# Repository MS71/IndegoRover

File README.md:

# IndegoRover
new MainBoard for Indego Lawn Mower

Prototype:

Schematic:
https://github.com/MS71/IndegoRover/blob/main/kicad/IndegoMower/pdf/IndegoMower.pdf

PCB:

Parts:
* ESP32 (S2/S3) Module (https://github.com/MS71/ROS2Mower/blob/master/hw/esp32_module.pdf)
* ARV Mega 128 for low level IO, security and motor driver
* origonal Indego connectors (26SHC-B-1A => mouser)
* DC motor driver: 3 * VNH2SP30 module (41V, 30A H Bridge)
* GPS receiver (ZED-F9P) (https://www.ardusimple.com/product/simplertk2blite/)
* 5 pin header for low cost, non RTK GPS receiver
* 10 Pin RPI Connector (5V, 3.3V, GND, I2C, UART)
* 10 Pin I2C Bus Connector
* 6 Pin I2C Bus Connector
* 5V Step Down Converter
* Bat Charger Circuit (Compatible with Indego Charge Station, difficult)
* Bat Charger Circuit (Compatible with std. 36V solar panel)
* Coil Sensor Amp
* low power + standby
* support for all available sensors
* BNO055 IMU module headers
* support for all sensors (bumper, coil fensem ...)
* power supply for onboard computer
* beeper
* support for LCD and keyboard (difficult)
* some breadboard area for custom extensions
* ...

onboard ROS2 computer: (optional)
* RPI4 or RPI Zero 2W headers 
* Orange Pi Zero 2 headers (http://www.orangepi.org/Orange%20Pi%20Zero2/)
* ...

Other:
* made with free Eagle  (max. 80 qcm) or kicad6

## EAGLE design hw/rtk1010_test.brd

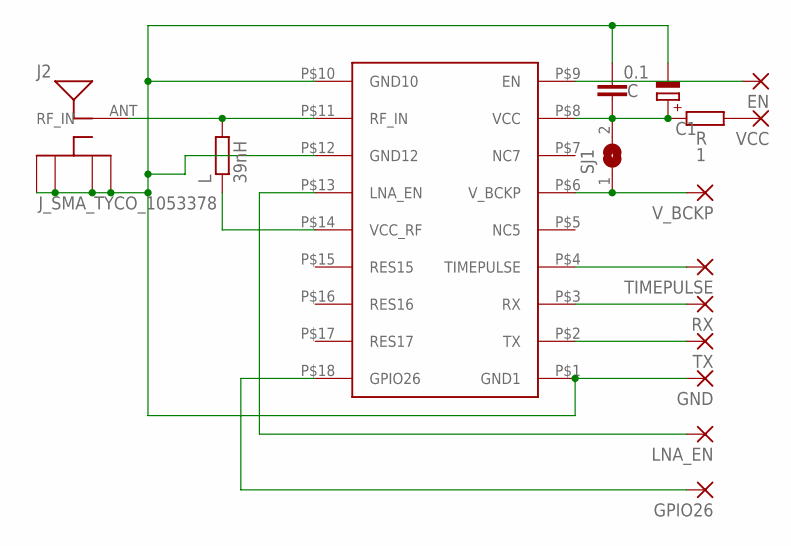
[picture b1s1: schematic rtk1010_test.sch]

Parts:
C: 0.1; C0805
C1: CPOL-EUSMCB; SMC_B
EN: 2,15/1,0
GND: 2,15/1,0
GPIO26: 2,15/1,0
J2: J_SMA_TYCO_1053378; 1053378-1
L: 39nH; R0805
LNA_EN: 2,15/1,0
R: 1; R0805
RX: 2,15/1,0
SJ1: SJW
TIMEPULSE: 2,15/1,0
TX: 2,15/1,0
U$1: RTK-1010
VCC: 2,15/1,0
V_BCKP: 2,15/1,0

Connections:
EN: EN.1, U$1.P$9 (EN)
GND: C.2, C1.-, GND.1, J2.GND_1 (RFGND_1), J2.GND_2 (RFGND_2), J2.GND_3 (RFGND_3), J2.GND_4 (RFGND_4), U$1.P$1 (GND1), U$1.P$10 (GND10), U$1.P$12 (GND12)
GPIO26: GPIO26.1, U$1.P$18 (GPIO26)
LNA_EN: LNA_EN.1, U$1.P$13 (LNA_EN)
unnamed: L.1, U$1.P$14 (VCC_RF)
unnamed: R.2, VCC.1
RF_IN: J2.ANT (RF_IN), L.2, U$1.P$11 (RF_IN)
RX: RX.1, U$1.P$3 (RX)
TIMEPULSE: TIMEPULSE.1, U$1.P$4 (TIMEPULSE)
TX: TX.1, U$1.P$2 (TX)
VCC: C.1, C1.+, R.1, SJ1.2, U$1.P$8 (VCC)
V_BKUP: SJ1.1, U$1.P$6 (V_BCKP), V_BCKP.1

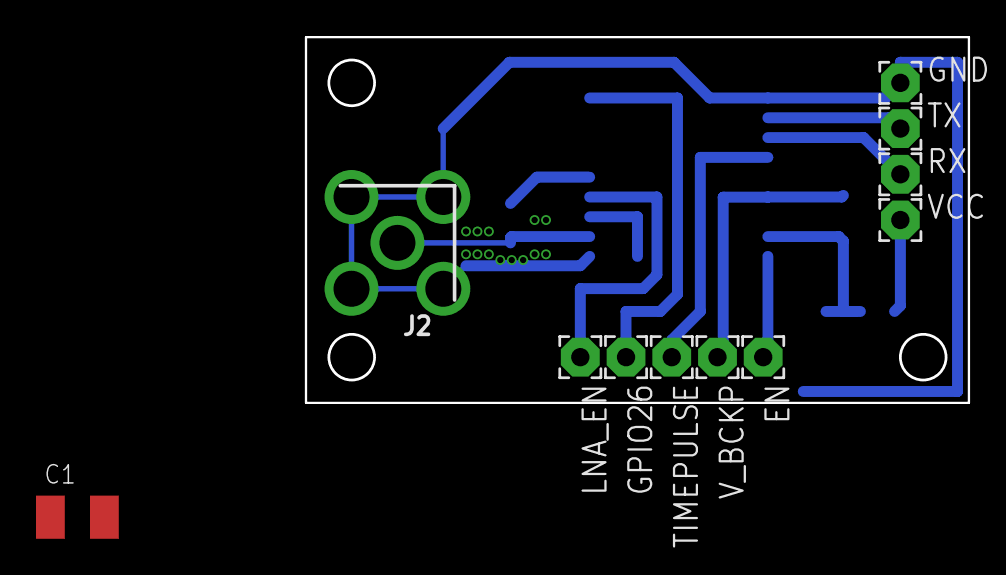
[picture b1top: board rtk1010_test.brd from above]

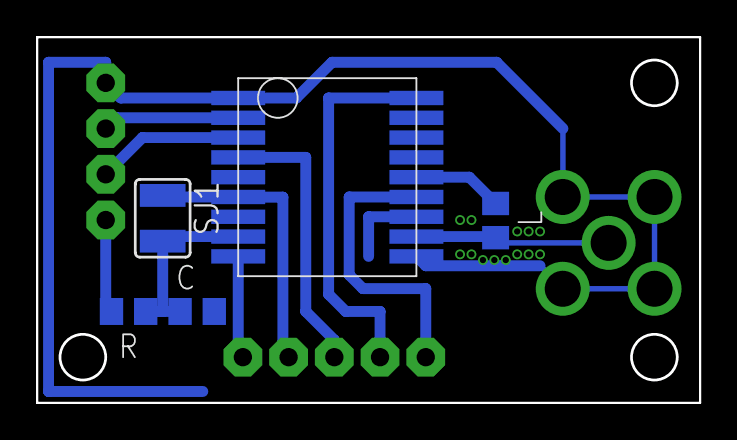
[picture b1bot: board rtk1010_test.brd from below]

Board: 2 copper layers, 36.8 x 20.3 mm, 16 parts (5 on the bottom side), 12 nets.

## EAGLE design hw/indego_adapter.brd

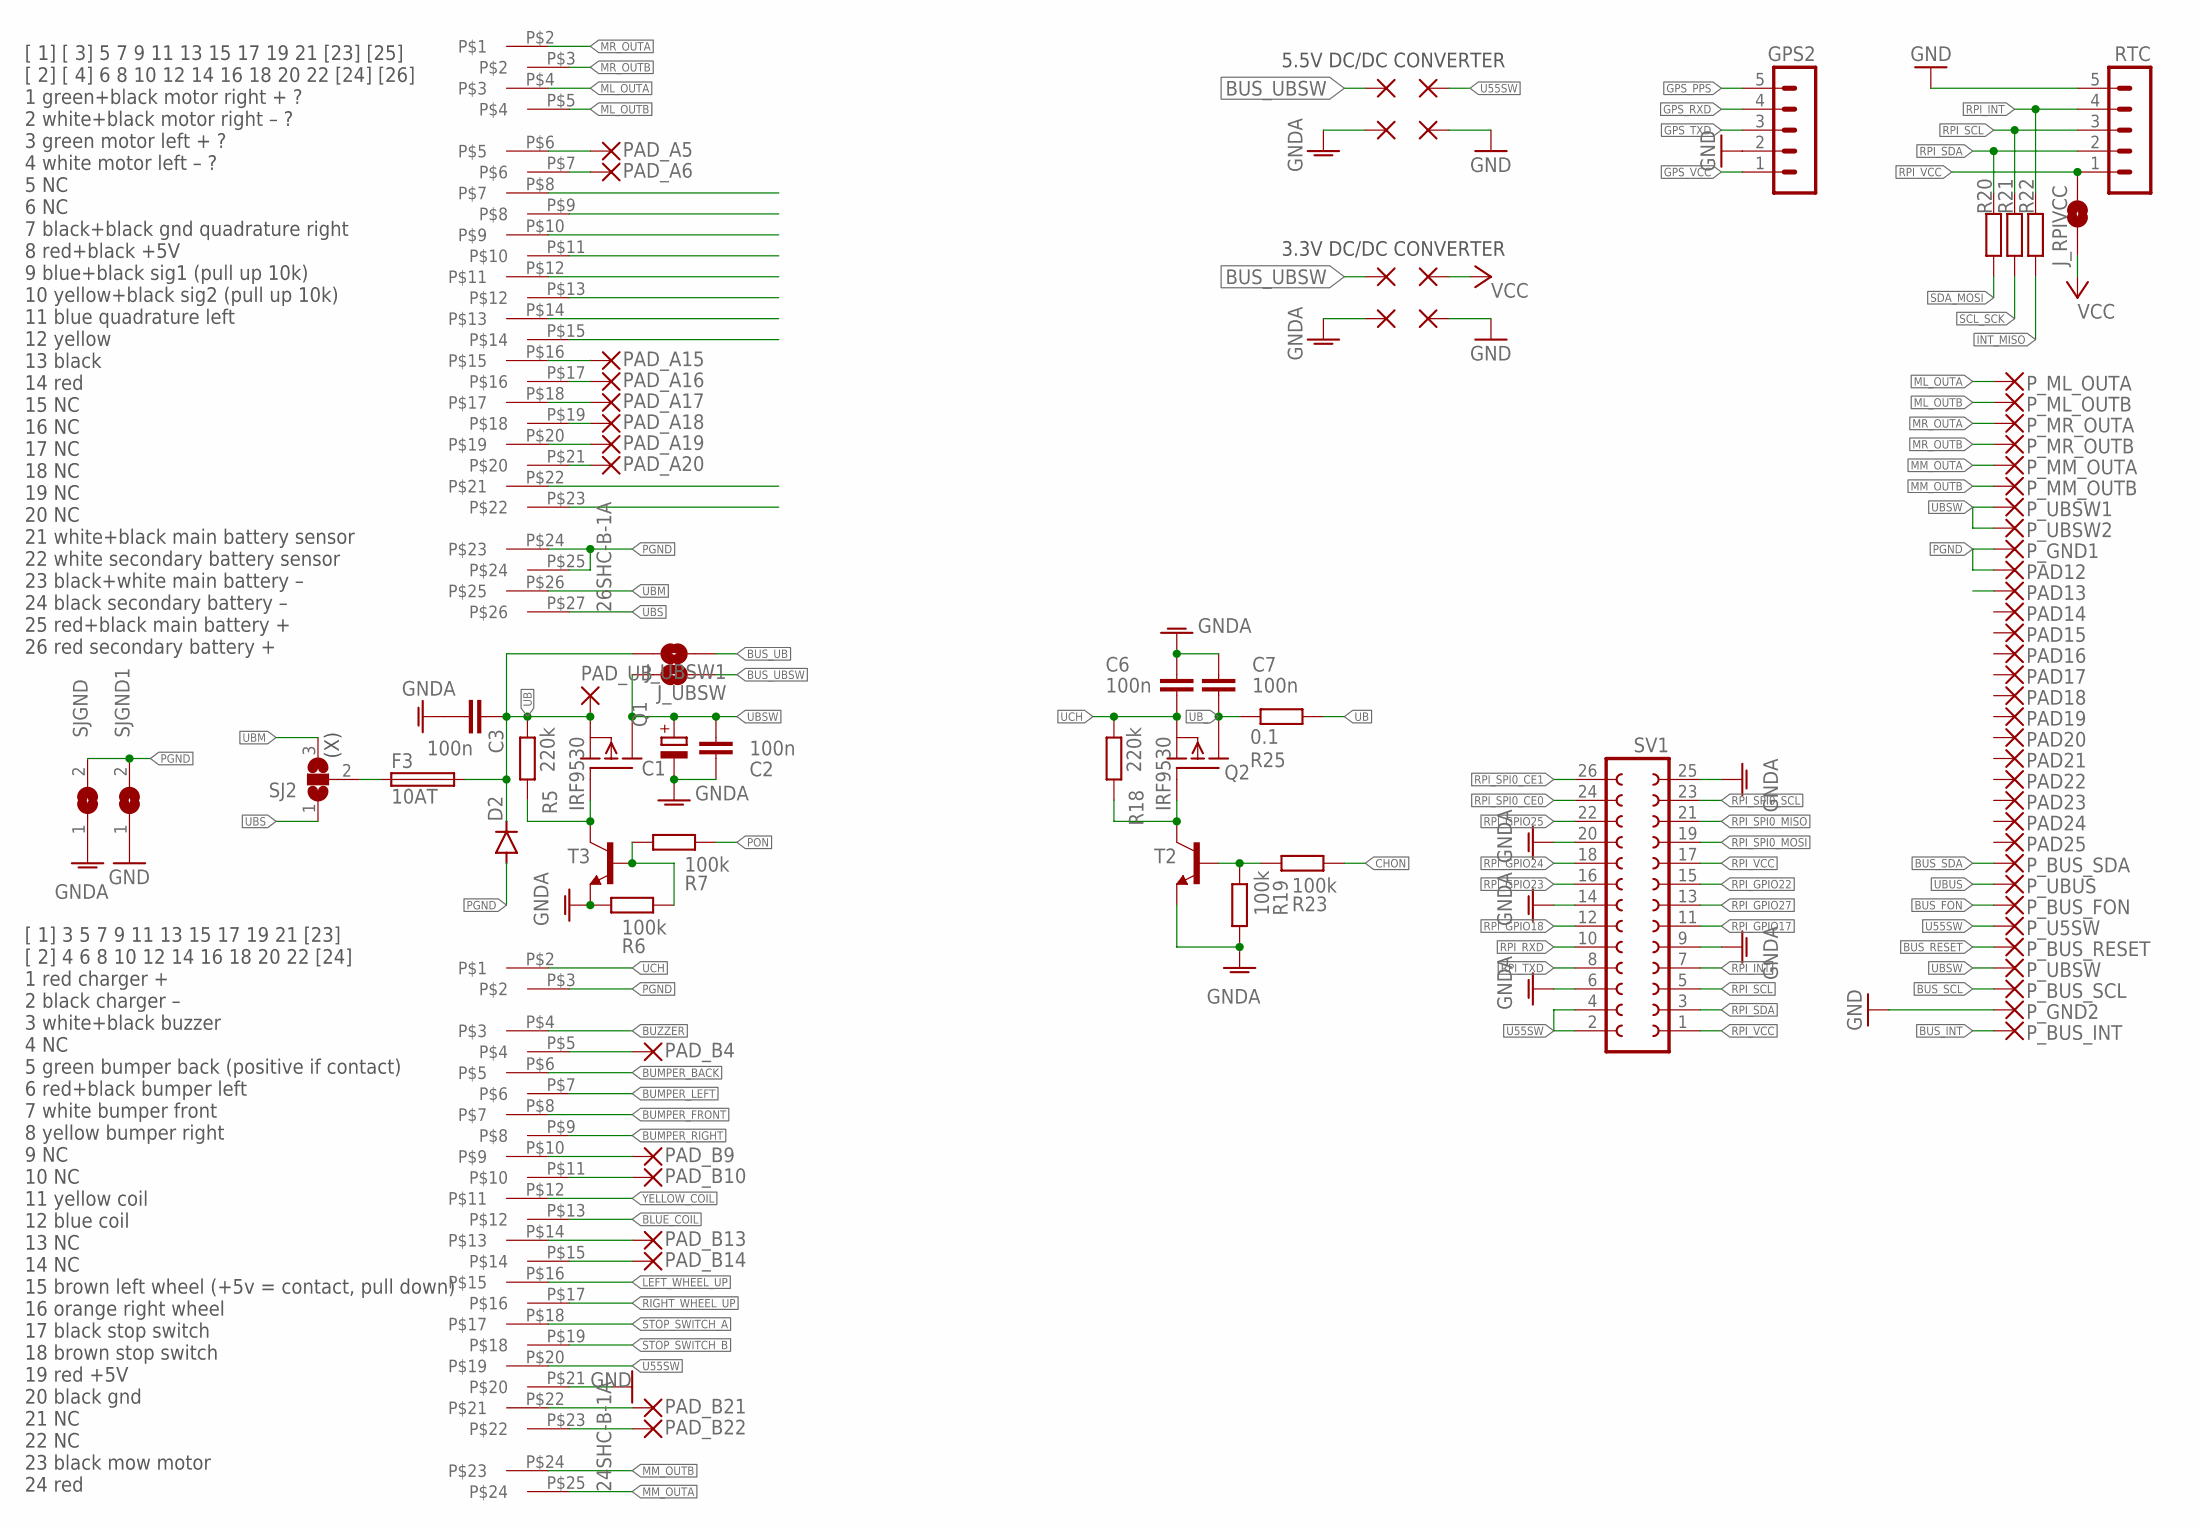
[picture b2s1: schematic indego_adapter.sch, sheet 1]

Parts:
C1: CPOL-EUE7.5-16; E7,5-16
C2, C3, C6, C7: 100n; C0805
D2: DIODE-MELF-MLL41; MELF-MLL41
DC_GND1, DC_GND2, DC_GND3, DC_GND4: 2,54/1,0
DC_VIN1, DC_VIN2: 2,54/1,0
F3: 10AT; SH22,5A
GPS2: MA05-1
J_RPIVCC: JUMPER-SMT_2_NO_NO-SILK; SMT-JUMPER_2_NO_NO-SILK
J_UBSW, J_UBSW1: JUMPER-SMT_2_NO_NO-SILK; SMT-JUMPER_2_NO_NO-SILK
PAD12, PAD13, PAD14, PAD15, PAD16, PAD17, PAD18, PAD19, PAD20, PAD21, PAD22, PAD23, PAD24, PAD25: 2,15/1,0
PAD_A5, PAD_A6, PAD_A15, PAD_A16, PAD_A17, PAD_A18, PAD_A19, PAD_A20: 1,6/0,9
PAD_B4, PAD_B9, PAD_B10, PAD_B13, PAD_B14, PAD_B21, PAD_B22: 1,6/0,9
PAD_UB: 3,17/1,3
P_BUS_FON: 2,15/1,0
P_BUS_INT: 2,15/1,0
P_BUS_RESET: 2,15/1,0
P_BUS_SCL: 2,15/1,0
P_BUS_SDA: 2,15/1,0
P_GND1, P_GND2: 2,15/1,0
P_ML_OUTA: 2,15/1,0
P_ML_OUTB: 2,15/1,0
P_MM_OUTA: 2,15/1,0
P_MM_OUTB: 2,15/1,0
P_MR_OUTA: 2,15/1,0
P_MR_OUTB: 2,15/1,0
P_U5SW: 2,15/1,0
P_UBSW, P_UBSW1, P_UBSW2: 2,15/1,0
P_UBUS: 2,15/1,0
Q1, Q2: IRF9530; TO220
R5, R18: 220k; R0805
R6, R7, R19, R23: 100k; R0805
R20, R21, R22: R-EU_M0805; M0805
R25: 0.1; R2512
RTC: MA05-1
SJ2: SJ2W; SJ_2
SJGND, SJGND1: SJ
SV1: FE13-2
T2, T3: BC817-16-NPN-SOT23-BEC; SOT23-BEC
U55SW: 2,54/1,0
U$1: 26SHC-B-1A
U$3: 24SHC-B-1A
VCC: 2,54/1,0

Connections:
BLUE_COIL: U$3.P$13
BUMPER_BACK: U$3.P$6
BUMPER_FRONT: U$3.P$8
BUMPER_LEFT: U$3.P$7
BUMPER_RIGHT: U$3.P$9
BUS_FON: P_BUS_FON.1; also elsewhere on the board
BUS_INT: P_BUS_INT.1; also elsewhere on the board
BUS_RESET: P_BUS_RESET.1; also elsewhere on the board
BUS_SCL: P_BUS_SCL.1; also elsewhere on the board
BUS_SDA: P_BUS_SDA.1; also elsewhere on the board
BUS_UB: J_UBSW1.2; also elsewhere on the board
BUS_UBSW: DC_VIN1.1, DC_VIN2.1, J_UBSW.2; also elsewhere on the board
BUZZER: U$3.P$4
CHON: R23.2
GND: DC_GND2.1, DC_GND4.1, GPS2.2, P_GND2.1, RTC.5, SJGND1.1, U$3.P$21; also elsewhere on the board
GNDA: C1.-, C2.2, C3.2, C6.1, C7.1, DC_GND1.1, DC_GND3.1, R6.1, R19.1, SJGND.1, SV1.6, SV1.9, SV1.14, SV1.20, SV1.25, T2.E, T3.E
GPS_PPS: GPS2.5
GPS_RXD: GPS2.4; also elsewhere on the board
GPS_TXD: GPS2.3; also elsewhere on the board
GPS_VCC: GPS2.1; also elsewhere on the board
INT_MISO: R22.1
LEFT_WHEEL_UP: U$3.P$16
ML_OUTA: P_ML_OUTA.1, U$1.P$4; also elsewhere on the board
ML_OUTB: P_ML_OUTB.1, U$1.P$5; also elsewhere on the board
MM_OUTA: P_MM_OUTA.1, U$3.P$25; also elsewhere on the board
MM_OUTB: P_MM_OUTB.1, U$3.P$24; also elsewhere on the board
MR_OUTA: P_MR_OUTA.1, U$1.P$2; also elsewhere on the board
MR_OUTB: P_MR_OUTB.1, U$1.P$3; also elsewhere on the board
unnamed: Q2.1 (G), R18.2, T2.C
unnamed: PAD_B4.1, U$3.P$5
unnamed: PAD_A5.1, U$1.P$6
unnamed: PAD_A6.1, U$1.P$7
unnamed: PAD_A15.1, U$1.P$16
unnamed: PAD_A16.1, U$1.P$17
unnamed: PAD_A17.1, U$1.P$18
unnamed: PAD_A18.1, U$1.P$19
unnamed: PAD_A19.1, U$1.P$20
unnamed: PAD_A20.1, U$1.P$21
unnamed: PAD_B9.1, U$3.P$10
unnamed: PAD_B10.1, U$3.P$11
unnamed: R6.2, R7.1, T3.B
unnamed: Q1.1 (G), R5.2, T3.C
unnamed: PAD_B13.1, U$3.P$14
unnamed: PAD_B14.1, U$3.P$15
unnamed: PAD_B21.1, U$3.P$22
unnamed: PAD_B22.1, U$3.P$23
unnamed: R19.2, R23.1, T2.B
PGND: D2.A, PAD12.1, P_GND1.1, SJGND.2, SJGND1.2, U$1.P$24, U$1.P$25, U$3.P$3; also elsewhere on the board
PON: R7.2
RIGHT_WHEEL_UP: U$3.P$17
RPI_GPIO17: SV1.11
RPI_GPIO18: SV1.12
RPI_GPIO22: SV1.15
RPI_GPIO23: SV1.16
RPI_GPIO24: SV1.18
RPI_GPIO25: SV1.22
RPI_GPIO27: SV1.13
RPI_INT: R22.2, RTC.4, SV1.7
RPI_RXD: SV1.10
RPI_SCL: R21.2, RTC.3, SV1.5
RPI_SDA: R20.2, RTC.2, SV1.3
RPI_SPI0_CE0: SV1.24
RPI_SPI0_CE1: SV1.26
RPI_SPI0_MISO: SV1.21
RPI_SPI0_MOSI: SV1.19
RPI_SPI0_SCL: SV1.23
RPI_TXD: SV1.8
RPI_VCC: J_RPIVCC.1, RTC.1, SV1.1, SV1.17
SCL_SCK: R21.1; also elsewhere on the board
SDA_MOSI: R20.1; also elsewhere on the board
STOP_SWITCH_A: U$3.P$18
STOP_SWITCH_B: U$3.P$19
U55SW: P_U5SW.1, SV1.2, SV1.4, U55SW.1, U$3.P$20; also elsewhere on the board
UB: C3.1, D2.C, F3.2, J_UBSW1.1, PAD_UB.1, Q1.3 (S), R5.1, R25.2
UBM: SJ2.3, U$1.P$26
UBS: SJ2.1, U$1.P$27
UBSW: C1.+, C2.1, J_UBSW.1, P_UBSW.1, P_UBSW1.1, P_UBSW2.1, Q1.2 (D); also elsewhere on the board
UBUS: P_UBUS.1; also elsewhere on the board
UBX: F3.1, SJ2.2
UB_: C7.2, Q2.2 (D), R25.1
UCH: C6.2, Q2.3 (S), R18.1, U$3.P$2
VCC: J_RPIVCC.2, VCC.1; also elsewhere on the board
YELLOW_COIL: U$3.P$12

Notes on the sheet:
[ 1] [ 3] 5 7 9 11 13 15 17 19 21 [23] [25] [ 2] [ 4] 6 8 10 12 14 16 18 20 22 [24] [26] 1 green+black motor right + ? 2 white+black motor right – ? 3 green motor left + ? 4 white motor left – ? 5 NC 6 NC 7 black+black gnd quadrature right 8 red+black +5V 9 blue+black sig1 (pull up 10k) 10 yellow+b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
[ 1] 3 5 7 9 11 13 15 17 19 21 [23] [ 2] 4 6 8 10 12 14 16 18 20 22 [24] 1 red charger + 2 black charger – 3 white+black buzzer 4 NC 5 green bumper back (positive if contact) 6 red+black bumper left 7 white bumper front 8 yellow bumper right 9 NC 10 NC 11 yellow coil 12 blue coil 13 NC 14 NC 15 bro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
(X)
5.5V DC/DC CONVERTER
3.3V DC/DC CONVERTER

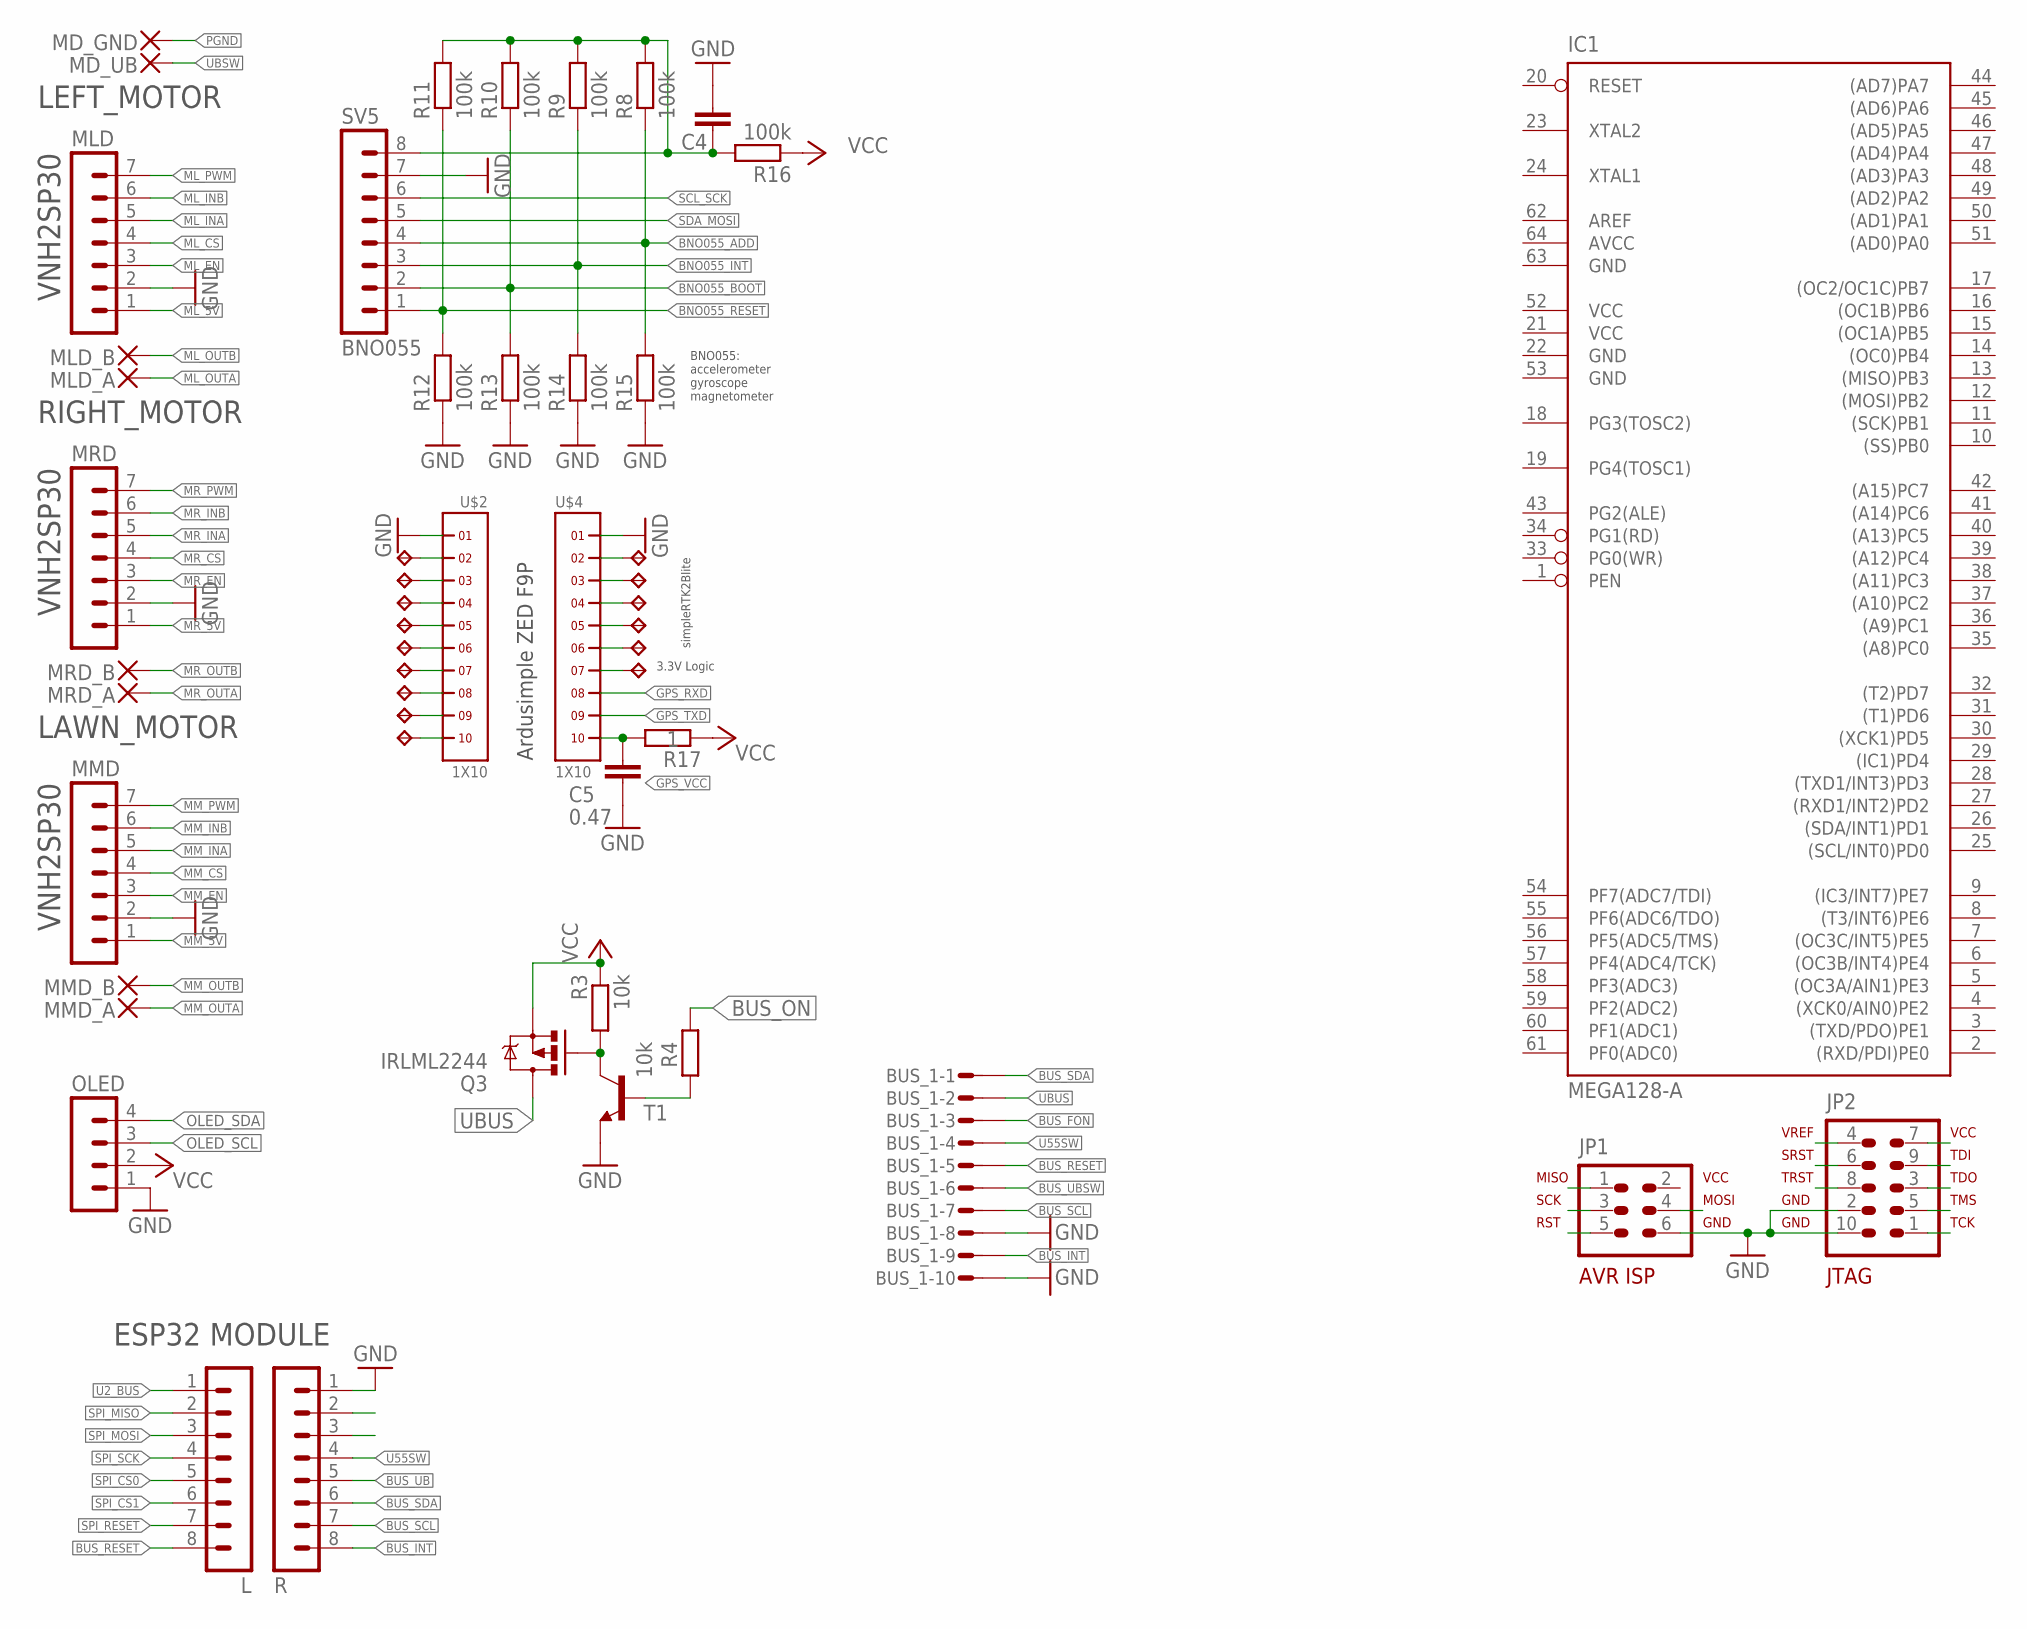
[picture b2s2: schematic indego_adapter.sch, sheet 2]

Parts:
BUS_1: I2CBUS; MICROMATCH-10SMD
C4: C-EUC0805; C0805
C5: 0.47; C0805
IC1: MEGA128-A; TQFP64
JP1: AVR-ISP-6VERT; AVR-ISP-6
JP2: AVR-JTAG-10
L: MA08-1
MD_GND: 3,17/1,3
MD_UB: 3,17/1,3
MLD: MA07-1
MLD_A: 3,17/1,3
MLD_B: 3,17/1,3
MMD: MA07-1
MMD_A: 3,17/1,3
MMD_B: 3,17/1,3
MRD: MA07-1
MRD_A: 3,17/1,3
MRD_B: 3,17/1,3
OLED: MA04-1
Q3: IRLML2244; SOT23-3
R: MA08-1
R3, R4: 10k; R0805
R8, R9, R10, R11, R12, R13, R14, R15, R16: 100k; M0805
R17: 1; M0805
SV5: BNO055; MA08-1
T1: BC817-16-NPN-SOT23-BEC; SOT23-BEC
TP1, TP2, TP3, TP4, TP5, TP6, TP7, TP8, TP9, TP10, TP11, TP12, TP13, TP14, TP15: TPB2,54; B2,54
U$2, U$4: 1X10

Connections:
AVCC: IC1.64 (AVCC)
BNO055_ADD: R8.1, R15.2, SV5.4
BNO055_BOOT: R10.1, R13.2, SV5.2
BNO055_INT: R9.1, R14.2, SV5.3
BNO055_RESET: R11.1, R12.2, SV5.1
BUS_FON: BUS_1.3; also elsewhere on the board
BUS_INT: BUS_1.9, R.8; also elsewhere on the board
BUS_ON: R4.1
BUS_RESET: BUS_1.5, L.8; also elsewhere on the board
BUS_SCL: BUS_1.7, R.7; also elsewhere on the board
BUS_SDA: BUS_1.1, R.6; also elsewhere on the board
BUS_UB: R.5; also elsewhere on the board
BUS_UBSW: BUS_1.6; also elsewhere on the board
GND: BUS_1.8, BUS_1.10, C4.1, C5.2, IC1.22 (GND), IC1.53 (GND), IC1.63 (GND), JP1.6, JP2.2, JP2.10, MLD.2, MMD.2, MRD.2, OLED.1, R.1, R12.1, R13.1, R14.1, R15.1, SV5.7, T1.E, U$2.1, U$4.1; also elsewhere on the board
GPS_RXD: U$4.8; also elsewhere on the board
GPS_TXD: U$4.9; also elsewhere on the board
GPS_VCC: C5.1, R17.2, U$4.10; also elsewhere on the board
ML_5V: MLD.1
ML_CS: MLD.4
ML_EN: MLD.3
ML_INA: MLD.5
ML_INB: MLD.6
ML_OUTA: MLD_A.1; also elsewhere on the board
ML_OUTB: MLD_B.1; also elsewhere on the board
ML_PWM: MLD.7
MM_5V: MMD.1
MM_CS: MMD.4
MM_EN: MMD.3
MM_INA: MMD.5
MM_INB: MMD.6
MM_OUTA: MMD_A.1; also elsewhere on the board
MM_OUTB: MMD_B.1; also elsewhere on the board
MM_PWM: MMD.7
MR_5V: MRD.1
MR_CS: MRD.4
MR_EN: MRD.3
MR_INA: MRD.5
MR_INB: MRD.6
MR_OUTA: MRD_A.1; also elsewhere on the board
MR_OUTB: MRD_B.1; also elsewhere on the board
MR_PWM: MRD.7
unnamed: TP1.TP, U$2.2
unnamed: Q3.1 (G), R3.2, T1.C
unnamed: R4.2, T1.B
unnamed: C4.2, R8.2, R9.2, R10.2, R11.2, R16.2, SV5.8
unnamed: TP2.TP, U$2.3
unnamed: TP3.TP, U$2.4
unnamed: TP4.TP, U$2.5
unnamed: TP5.TP, U$2.6
unnamed: TP6.TP, U$2.7
unnamed: TP7.TP, U$2.8
unnamed: TP8.TP, U$2.9
unnamed: TP9.TP, U$2.10
unnamed: TP10.TP, U$4.2
unnamed: TP11.TP, U$4.3
unnamed: TP12.TP, U$4.4
unnamed: TP13.TP, U$4.5
unnamed: TP14.TP, U$4.6
unnamed: TP15.TP, U$4.7
OLED_SCL: OLED.3
OLED_SDA: OLED.4
PGND: MD_GND.1; also elsewhere on the board
SCL_SCK: SV5.6; also elsewhere on the board
SDA_MOSI: SV5.5; also elsewhere on the board
SPI_CS0: L.5
SPI_CS1: L.6
SPI_MISO: L.2
SPI_MOSI: L.3
SPI_RESET: L.7
SPI_SCK: L.4
U2_BUS: L.1
U33A: R.2
U33B: R.3
U55SW: BUS_1.4, R.4; also elsewhere on the board
UBSW: MD_UB.1; also elsewhere on the board
UBUS: BUS_1.2, Q3.3 (D); also elsewhere on the board
VCC: IC1.21 (VCC), IC1.52 (VCC), OLED.2, Q3.2 (S), R3.1, R16.1, R17.1; also elsewhere on the board

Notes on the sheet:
LEFT_MOTOR
RIGHT_MOTOR
LAWN_MOTOR
VNH2SP30
ESP32 MODULE
Ardusimple ZED F9P
3.3V Logic
BNO055: accelerometer gyroscope magnetometer
simpleRTK2Blite

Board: 2 copper layers, 140 parts (30 on the bottom side), 76 nets, no tracks yet.

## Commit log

2022-03-21 added
2022-05-18 new kicad pcb added
2022-06-05 some more work
2022-06-05 pdf added
2022-06-05 3D image added
2022-06-15 rtk1010 board added
2022-06-15 rtk1010 board updated
2022-06-18 some optimiziations
2025-10-19 project restart 2025
2025-10-21 some further progress
2025-10-22 some work ...
2025-11-19 some more changes

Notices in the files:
parts and their libraries:
SparkFun-Jumpers: Licensing: Creative Commons ShareAlike 4.0 International - https://creativecommons.org/licenses/by-sa/4.0
